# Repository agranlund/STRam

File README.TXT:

----------------------------------------------------------------------------
4MB RAM expansion for Atari 520ST(M)
(c)2020, Anders Granlund
----------------------------------------------------------------------------
Tested on a C070243 Rev.I motherboard, your mileage may vary.
----------------------------------------------------------------------------

----------------------------------------------------------------------------
IMPORTANT:
----------------------------------------------------------------------------
There is a misstake on this board that needs fixing with
a bodge wire. See "board_fix.jpg" for where to solder
that wire.

----------------------------------------------------------------------------
BOM:
----------------------------------------------------------------------------
C1-C6 = 100nF (0805 size)
R1-R2 = 68 ohm (0805 size)
R3 = 33 ohm (0805 size)
2x 5118160 DRAM's in SOJ42 package

----------------------------------------------------------------------------
HOWTO:
----------------------------------------------------------------------------

* Desolder the existing RAM and solder the new board in
place. 

* Solder the bodge wire as seen in "board_fix.jpg"

* Solder the four wires from the RAM board header
to the motherboard (MAD9, CAS1L, CAS1H, RAS1)

All four signals can be found on the MMU and you can solder
to the socket pins on the underside of the motherboard.
Alternatively you may find solder points for CAS1L,CAS1H,RAS1
on the topside on some motherboards but MAD9 is normally only
found on the MMU.

MMU pins:
RAS1  = 18
CAS1L = 21
CAS1H = 22
MAD9  = 64

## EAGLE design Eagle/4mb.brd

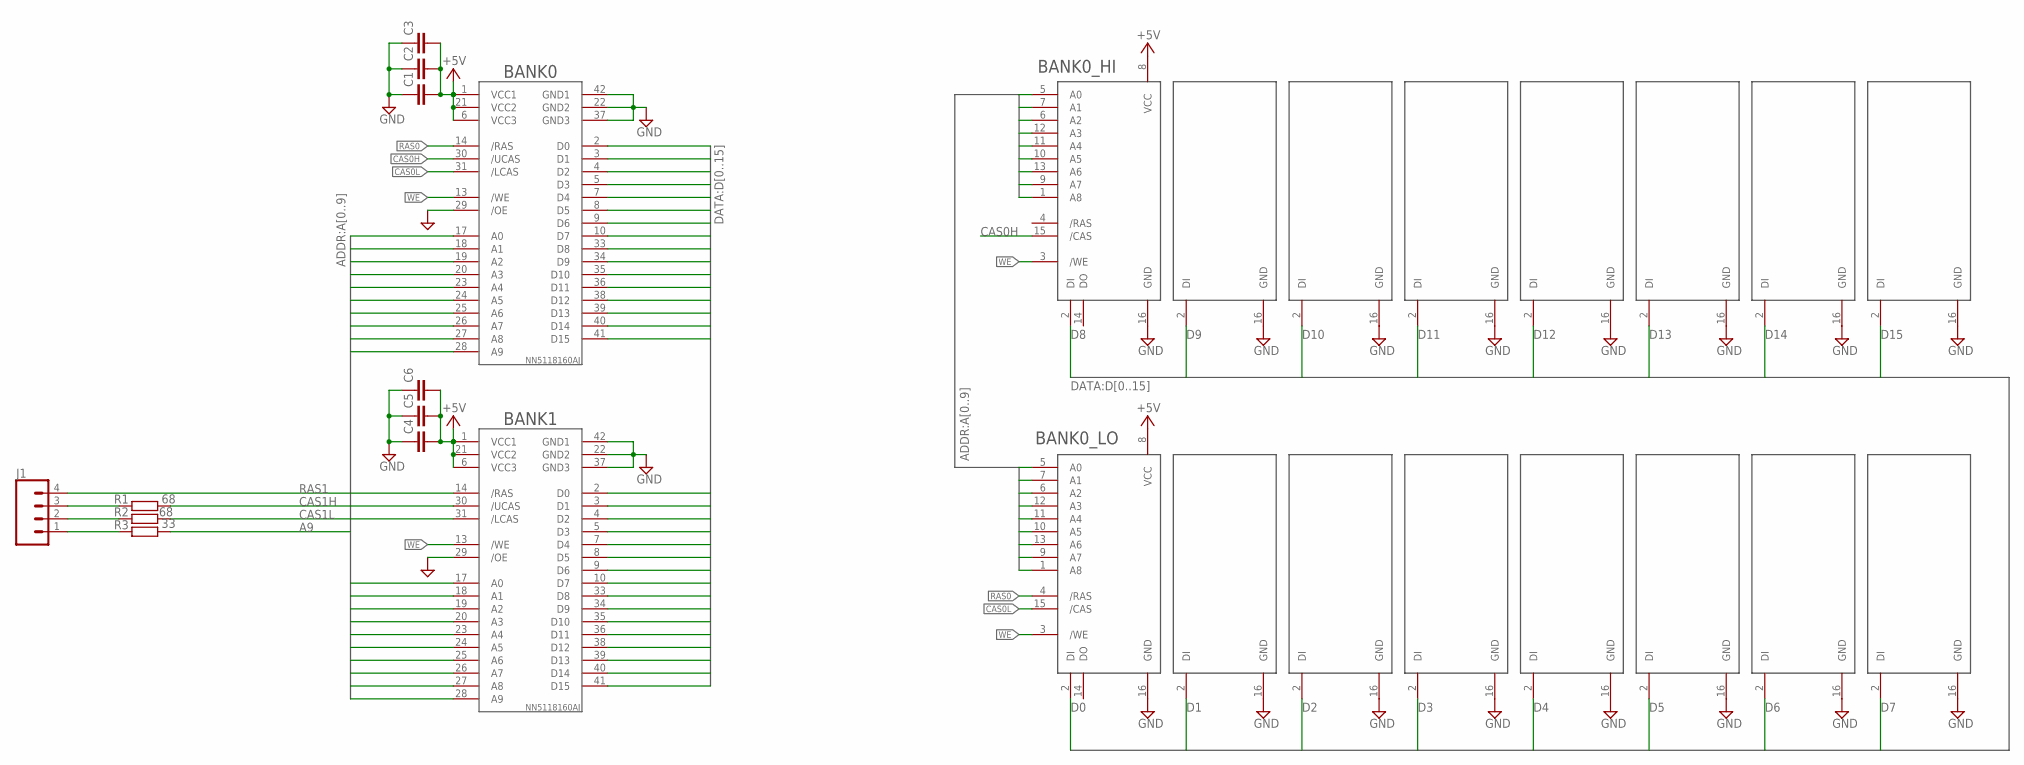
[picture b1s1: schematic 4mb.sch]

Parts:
C1, C2, C3, C4, C5, C6: C-EUC0805; C0805
J1: CONN_04PTH; 1X04
R1, R2: 68; R0805
R3: 33; R0805
U$1, U$2: NN5118160AJ; SOJ127P1117X376-42
U$3, U$11: ST_DRAM; DIL16
U$4, U$5, U$6, U$7, U$8, U$9, U$10, U$12, U$13, U$14, U$15, U$16, U$17, U$18: ST_DRAM_D; ST_DRAM_SOCKET_MINIMAL

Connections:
+5V: C1.2, C2.2, C3.2, C4.2, C5.2, C6.2, U$1.1 (VCC1), U$1.6 (VCC3), U$1.21 (VCC2), U$2.1 (VCC1), U$2.6 (VCC3), U$2.21 (VCC2), U$3.8 (VCC), U$11.8 (VCC)
A0: U$1.17 (A0), U$2.17 (A0), U$3.5 (A0), U$11.5 (A0)
A1: U$1.18 (A1), U$2.18 (A1), U$3.7 (A1), U$11.7 (A1)
A2: U$1.19 (A2), U$2.19 (A2), U$3.6 (A2), U$11.6 (A2)
A3: U$1.20 (A3), U$2.20 (A3), U$3.12 (A3), U$11.12 (A3)
A4: U$1.23 (A4), U$2.23 (A4), U$3.11 (A4), U$11.11 (A4)
A5: U$1.24 (A5), U$2.24 (A5), U$3.10 (A5), U$11.10 (A5)
A6: U$1.25 (A6), U$2.25 (A6), U$3.13 (A6), U$11.13 (A6)
A7: U$1.26 (A7), U$2.26 (A7), U$3.9 (A7), U$11.9 (A7)
A8: U$1.27 (A8), U$2.27 (A8), U$3.1 (A8), U$11.1 (A8)
A9: R3.2, U$1.28 (A9), U$2.28 (A9)
CAS0H: U$1.30 (/UCAS), U$3.15 (/CAS)
CAS0L: U$1.31 (/LCAS), U$11.15 (/CAS)
CAS1H: R1.2, U$2.30 (/UCAS)
CAS1L: R2.2, U$2.31 (/LCAS)
D0: U$1.2 (D0), U$2.2 (D0), U$11.2 (DI)
D1: U$1.3 (D1), U$2.3 (D1), U$12.2 (DI)
D2: U$1.4 (D2), U$2.4 (D2), U$13.2 (DI)
D3: U$1.5 (D3), U$2.5 (D3), U$14.2 (DI)
D4: U$1.7 (D4), U$2.7 (D4), U$15.2 (DI)
D5: U$1.8 (D5), U$2.8 (D5), U$16.2 (DI)
D6: U$1.9 (D6), U$2.9 (D6), U$17.2 (DI)
D7: U$1.10 (D7), U$2.10 (D7), U$18.2 (DI)
D8: U$1.33 (D8), U$2.33 (D8), U$3.2 (DI)
D9: U$1.34 (D9), U$2.34 (D9), U$4.2 (DI)
D10: U$1.35 (D10), U$2.35 (D10), U$5.2 (DI)
D11: U$1.36 (D11), U$2.36 (D11), U$6.2 (DI)
D12: U$1.38 (D12), U$2.38 (D12), U$7.2 (DI)
D13: U$1.39 (D13), U$2.39 (D13), U$8.2 (DI)
D14: U$1.40 (D14), U$2.40 (D14), U$9.2 (DI)
D15: U$1.41 (D15), U$2.41 (D15), U$10.2 (DI)
GND: C1.1, C2.1, C3.1, C4.1, C5.1, C6.1, U$1.22 (GND2), U$1.29 (/OE), U$1.37 (GND3), U$1.42 (GND1), U$2.22 (GND2), U$2.29 (/OE), U$2.37 (GND3), U$2.42 (GND1), U$3.16 (GND), U$4.16 (GND), U$5.16 (GND), U$6.16 (GND), U$7.16 (GND), U$8.16 (GND), U$9.16 (GND), U$10.16 (GND), U$11.16 (GND), U$12.16 (GND), U$13.16 (GND), U$14.16 (GND), U$15.16 (GND), U$16.16 (GND), U$17.16 (GND), U$18.16 (GND)
unnamed: J1.2, R2.1
unnamed: J1.1, R3.1
unnamed: J1.3, R1.1
RAS0: U$1.14 (/RAS), U$11.4 (/RAS)
RAS1: J1.4, U$2.14 (/RAS)
WE: U$1.13 (/WE), U$2.13 (/WE), U$3.3 (/WE), U$11.3 (/WE)

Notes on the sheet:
BANK0
BANK1
BANK0_HI
BANK0_LO

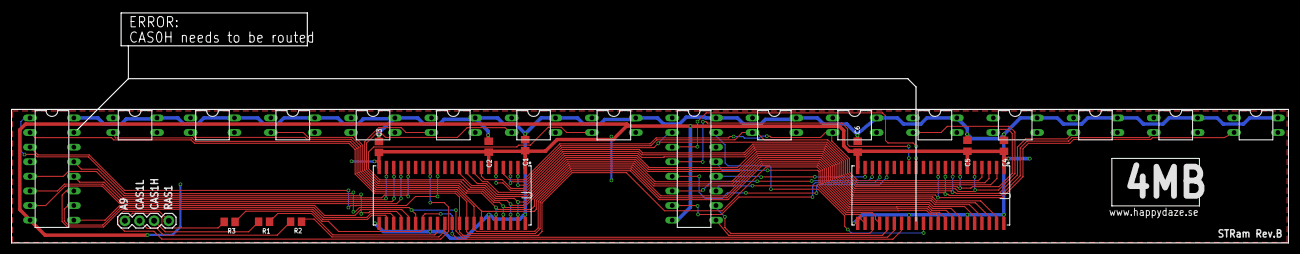
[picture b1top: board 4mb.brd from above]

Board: 2 copper layers, 221.9 x 40.1 mm, 28 parts (0 on the bottom side), 38 nets.

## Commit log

2021-12-19 Update README.TXT
    Updated readme to warn about installing sockets.
2021-12-20 Adjusted File Extensions
2021-12-20 Rewrote README

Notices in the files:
parts and their libraries:
SparkFun-Connectors: Licensing: Creative Commons ShareAlike 4.0 International - https://creativecommons.org/licenses/by-sa/4.0
